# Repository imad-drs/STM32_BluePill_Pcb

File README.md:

# STM32_BluePill_Pcb
A custom STM32F103C8T6 development board designed in KiCad

⚠️ Disclaimer: First PCB Project
**Please note:** This is my very first custom PCB design! I reverse-engineered the popular "Blue Pill" board to design this custom circuit in KiCad. It was created as a personal learning exercise to understand the bridge between embedded software and physical hardware. While I put a lot of effort into following best practices, there may be errors. **This project should not be used as an official hardware reference.**

## 🛠️ Project Overview
This repository contains the KiCad project files for a custom microcontroller development board based on the **STM32F103C8T6** (ARM Cortex-M3). 

### Hardware Specifications & Features:
* **PCB Stackup:** Routed on a standard 2-layer board.
* **Connectivity & Debugging:** Includes a dedicated **SWD (Serial Wire Debug)** header for easy flashing/debugging, plus broken-out **UART** and **I2C** pins for external sensor communication.
* **USB Interface:** Integrated Micro-USB Type-B connector for power and data.
* **Clocking:** External crystal oscillator circuit included for precise timing and USB synchronization.
* **User Interface:** Includes a dedicated BOOT button for flashing/configuration and a Power indicator LED.
* **Signal Integrity:** Robust power routing with separated digital and analog ground planes (where applicable).

## ⚡ Technical Deep Dive: Decoupling Capacitors
One of the primary focuses of this project was understanding and implementing proper power delivery. Because microcontrollers switch states millions of times per second, they require instantaneous bursts of current. Traces and power supplies have inherent inductance and cannot deliver this current fast enough, potentially causing the system to crash. 

To ensure stability, I implemented a strict decoupling strategy:
* **Local Decoupling (100nF):** Placed as close as physically possible to each `VDD` and `VBAT` pin. These act as tiny, instant energy reservoirs to handle high-frequency switching.
* **Bulk Decoupling (10uF):** Placed near the microcontroller to act as a larger, general energy reservoir for the IC.
* **Analog Filtering (VDDA):** The analog supply pin is highly sensitive to digital noise. I isolated it from the main digital 3.3V rail using a ferrite bead (120Ω at 100MHz) flanked by a 1uF and 10nF parallel capacitor network to protect the internal Analog-to-Digital Converters (ADCs).

## 📂 Files Included
* Core KiCad project files (`.kicad_pro`, `.kicad_sch`, `.kicad_pcb`).
* `Schematic.pdf`: Exported PDF of the logical circuit map.

---
*Designed by Drias Imad Eddine *

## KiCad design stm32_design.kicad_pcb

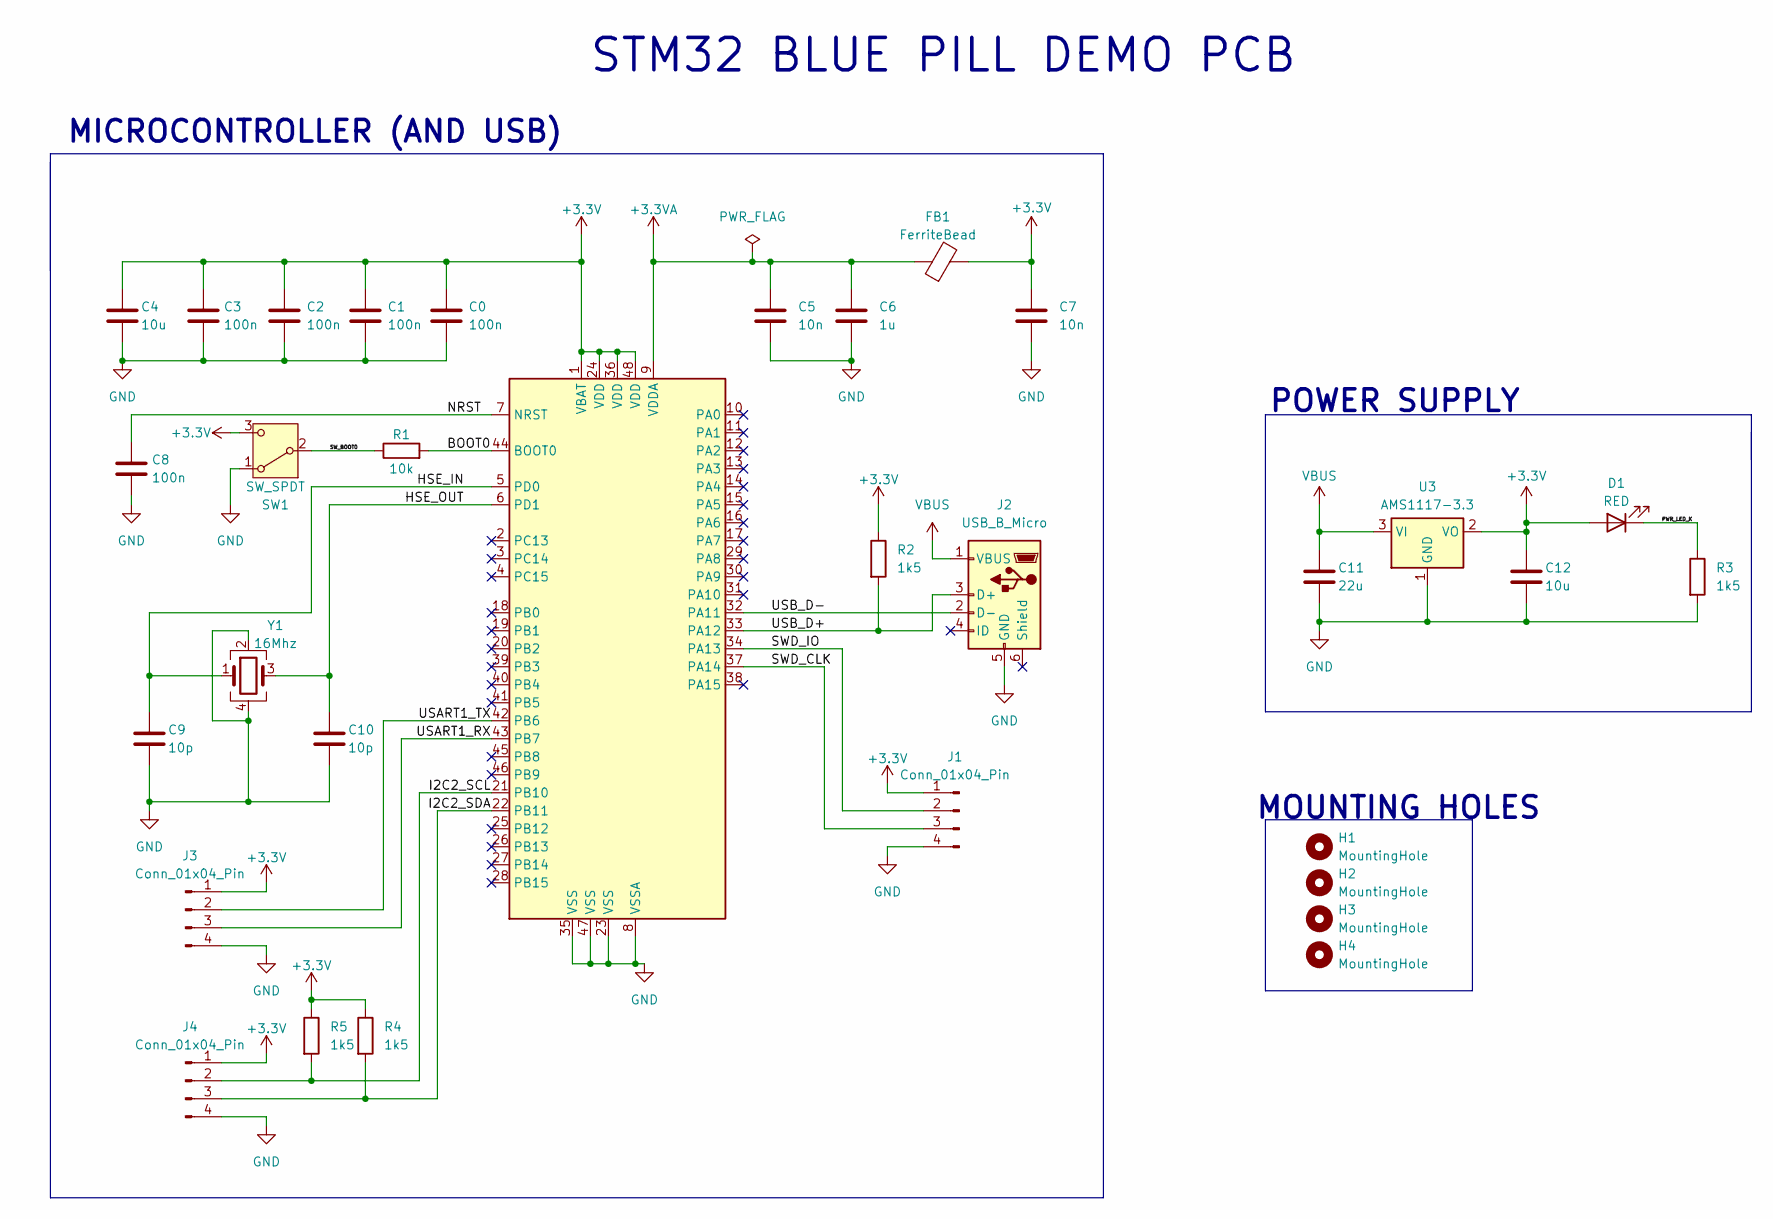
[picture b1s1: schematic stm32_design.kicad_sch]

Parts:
C0, C1, C2, C3, C8: 100n; C_0402_1005Metric
C4, C12: 10u; C_0402_1005Metric
C5, C7: 10n; C_0402_1005Metric
C6: 1u; C_0402_1005Metric
C9, C10: 10p; C_0402_1005Metric
C11: 22u; C_0402_1005Metric
D1: RED; LED_0603_1608Metric
FB1: FerriteBead; L_0603_1608Metric
H1, H2, H3, H4: MountingHole; MountingHole_2.2mm_M2
J1, J3, J4: Conn_01x04_Pin; PinHeader_1x04_P2.54mm_Vertical
J2: USB_B_Micro; USB_Micro-B_Wuerth_629105150521
R1: 10k; R_0402_1005Metric
R2, R3, R4, R5: 1k5; R_0402_1005Metric
SW1: SW_SPDT; SW_SPDT_PCM12
U1: STM32F103C8Tx; LQFP-48_7x7mm_P0.5mm
U3: AMS1117-3.3; SOT-223-3_TabPin2
Y1: 16Mhz; Crystal_SMD_3225-4Pin_3.2x2.5mm

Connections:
+3.3V: C0.1, C1.1, C2.1, C3.1, C4.1, C7.1, C12.1, D1.2 (A), FB1.2, J1.1, J3.1, J4.1, R2.1, R4.1, R5.1, SW1.3 (C), U1.1 (VBAT), U1.24 (VDD), U1.36 (VDD), U1.48 (VDD), U3.2 (VO)
+3.3VA: C5.1, C6.1, FB1.1, U1.9 (VDDA)
/BOOT0: R1.2, U1.44 (BOOT0)
/HSE_IN: C9.1, U1.5 (PD0), Y1.1
/HSE_OUT: C10.1, U1.6 (PD1), Y1.3
/I2C2_SCL: J4.2, R5.2, U1.21 (PB10)
/I2C2_SDA: J4.3, R4.2, U1.22 (PB11)
/NRST: C8.1, U1.7 (NRST)
/PWR_LED_K: D1.1 (K), R3.1
/SWD_CLK: J1.3, U1.37 (PA14)
/SWD_IO: J1.2, U1.34 (PA13)
/SW_BOOT0: R1.1, SW1.2 (B)
/USART1_RX: J3.3, U1.43 (PB7)
/USART1_TX: J3.2, U1.42 (PB6)
/USB_D+: J2.3 (D+), R2.2, U1.33 (PA12)
/USB_D-: J2.2 (D-), U1.32 (PA11)
GND: C0.2, C1.2, C2.2, C3.2, C4.2, C5.2, C6.2, C7.2, C8.2, C9.2, C10.2, C11.2, C12.2, J1.4, J2.5 (GND), J3.4, J4.4, R3.2, SW1.1 (A), U1.8 (VSSA), U1.23 (VSS), U1.35 (VSS), U1.47 (VSS), U3.1 (GND), Y1.2, Y1.4
VBUS: C11.1, J2.1 (VBUS), U3.3 (VI)

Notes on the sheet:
STM32 BLUE PILL DEMO PCB
POWER SUPPLY
MOUNTING HOLES
MICROCONTROLLER (AND USB)

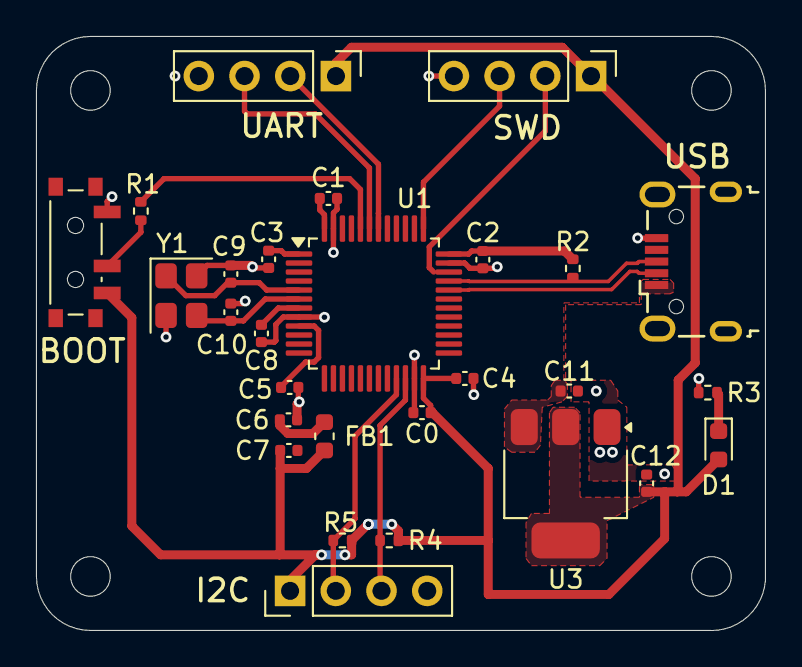
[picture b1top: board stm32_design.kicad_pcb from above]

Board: 2 copper layers, 40.5 x 33.0 mm, 32 parts (0 on the bottom side), 18 nets.

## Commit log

2026-03-16 Initial project upload
2026-03-16 Enhance README with project details and specifications
    Added detailed project overview, hardware specifications, and decoupling capacitor strategy to README.
